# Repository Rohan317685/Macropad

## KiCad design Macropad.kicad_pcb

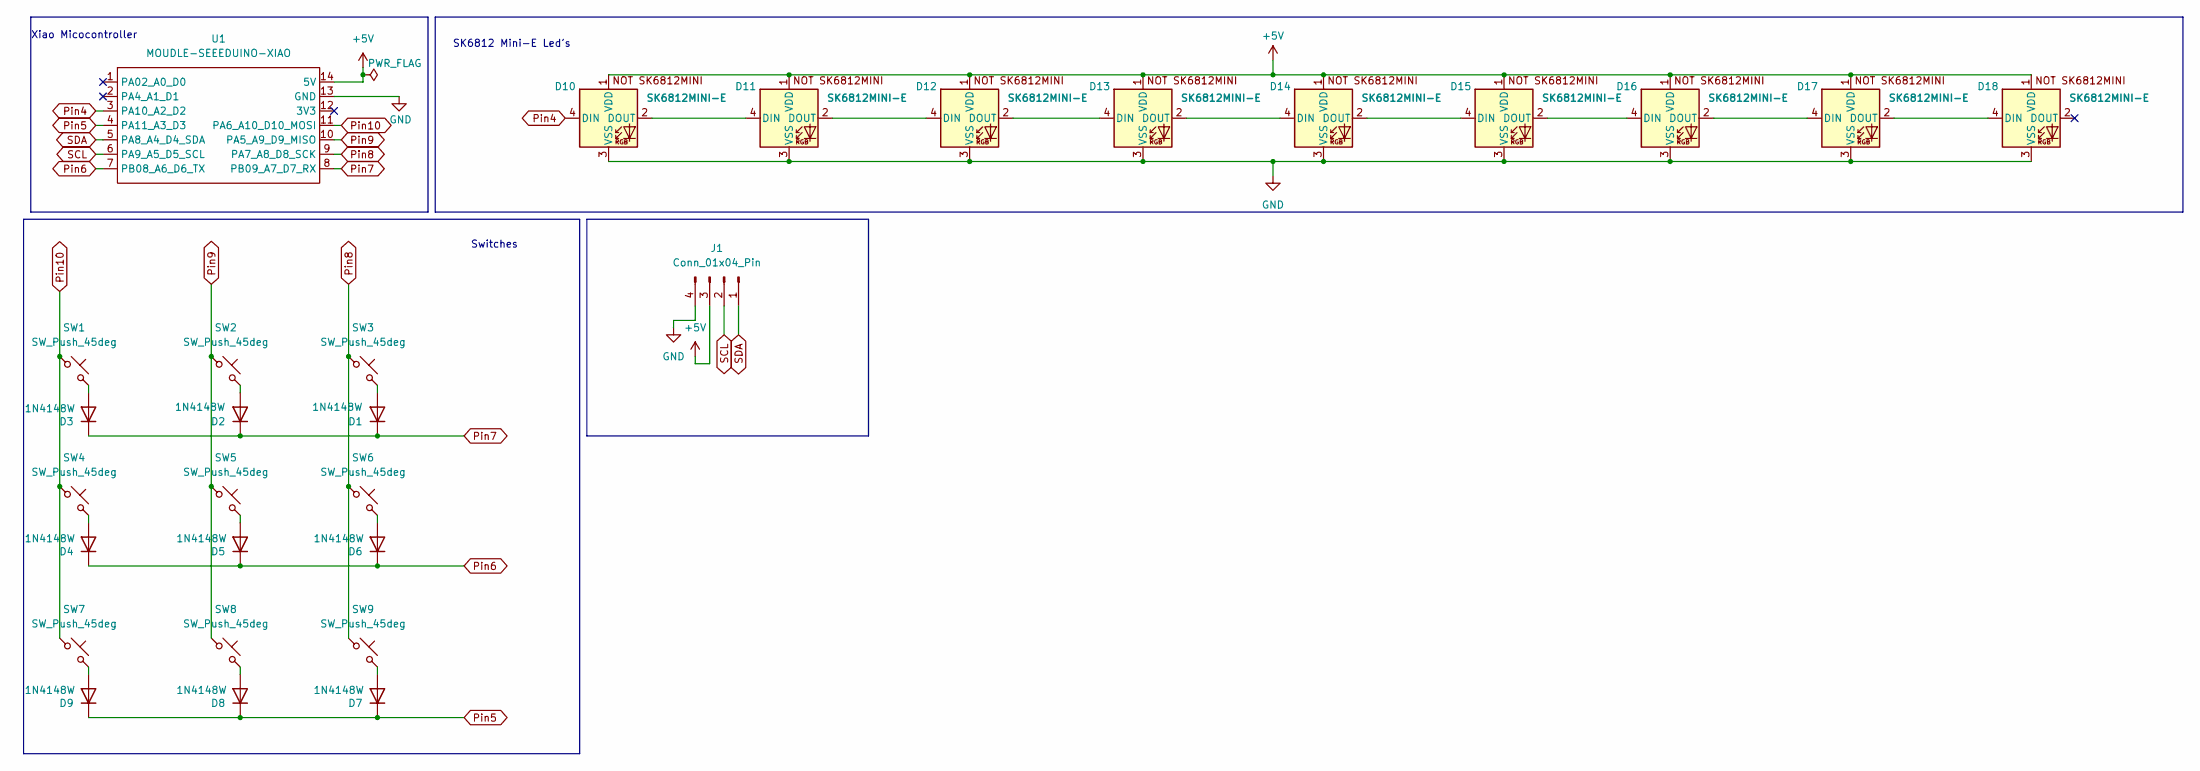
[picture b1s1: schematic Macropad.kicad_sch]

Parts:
D1, D2, D3, D4, D5, D6, D7, D8, D9: 1N4148W; D_SOD-123
D10, D11, D12, D13, D14, D15, D16, D17, D18: SK6812MINI-E; SK6812MINI-E_fixed
J1: Conn_01x04_Pin; SSD1306-0.91-OLED-4pin-128x32
SW1, SW2, SW3, SW4, SW5, SW6, SW7, SW8, SW9: SW_Push_45deg; SW_Cherry_MX_1.00u_PCB
U1: MOUDLE-SEEEDUINO-XIAO; XIAO-Generic-Hybrid-14P-2.54-21X17.8MM

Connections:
+5V: D10.1 (VDD), D11.1 (VDD), D12.1 (VDD), D13.1 (VDD), D14.1 (VDD), D15.1 (VDD), D16.1 (VDD), D17.1 (VDD), D18.1 (VDD), J1.3 (VCC), U1.14 (5V)
GND: D10.3 (VSS), D11.3 (VSS), D12.3 (VSS), D13.3 (VSS), D14.3 (VSS), D15.3 (VSS), D16.3 (VSS), D17.3 (VSS), D18.3 (VSS), J1.4 (GND), U1.13 (GND)
unnamed: D1.2 (A), SW3.2
unnamed: D2.2 (A), SW2.2
unnamed: D3.2 (A), SW1.2
unnamed: D4.2 (A), SW4.2
unnamed: D5.2 (A), SW5.2
unnamed: D6.2 (A), SW6.2
unnamed: D7.2 (A), SW9.2
unnamed: D8.2 (A), SW8.2
unnamed: D9.2 (A), SW7.2
unnamed: D10.2 (DOUT), D11.4 (DIN)
unnamed: D11.2 (DOUT), D12.4 (DIN)
unnamed: D12.2 (DOUT), D13.4 (DIN)
unnamed: D13.2 (DOUT), D14.4 (DIN)
unnamed: D14.2 (DOUT), D15.4 (DIN)
unnamed: D15.2 (DOUT), D16.4 (DIN)
unnamed: D16.2 (DOUT), D17.4 (DIN)
unnamed: D17.2 (DOUT), D18.4 (DIN)
Pin4: D10.4 (DIN), U1.3 (PA10_A2_D2)
Pin5: D7.1 (K), D8.1 (K), D9.1 (K), U1.4 (PA11_A3_D3)
Pin6: D4.1 (K), D5.1 (K), D6.1 (K), U1.7 (PB08_A6_D6_TX)
Pin7: D1.1 (K), D2.1 (K), D3.1 (K), U1.8 (PB09_A7_D7_RX)
Pin8: SW3.1, SW6.1, SW9.1, U1.9 (PA7_A8_D8_SCK)
Pin9: SW2.1, SW5.1, SW8.1, U1.10 (PA5_A9_D9_MISO)
Pin10: SW1.1, SW4.1, SW7.1, U1.11 (PA6_A10_D10_MOSI)
SCL: J1.2 (SCL), U1.6 (PA9_A5_D5_SCL)
SDA: J1.1 (SDA), U1.5 (PA8_A4_D4_SDA)

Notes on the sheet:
Switches
SK6812 Mini-E Led's
Xiao Micocontroller

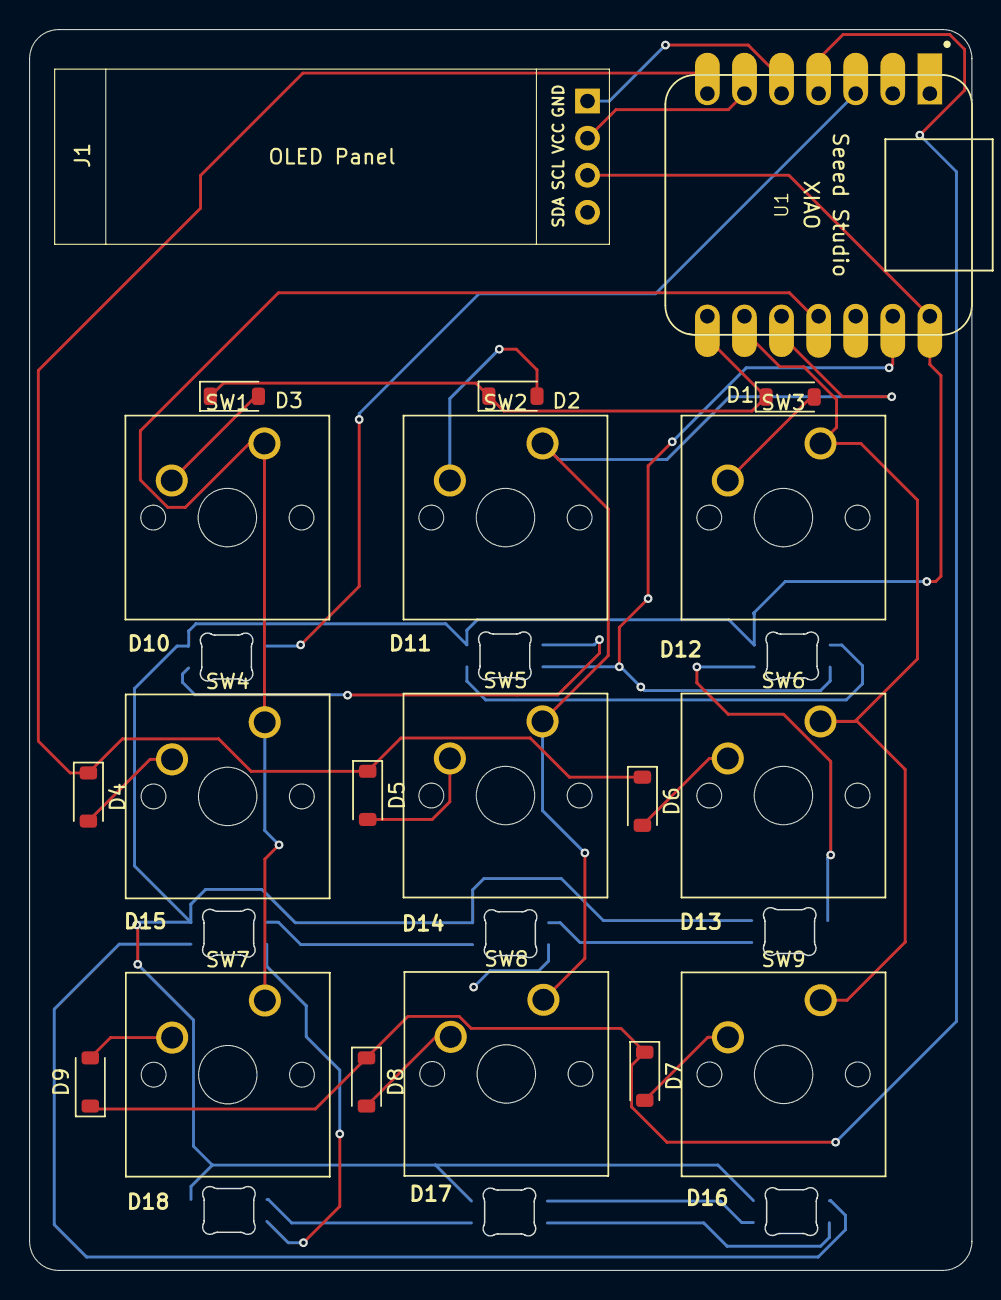
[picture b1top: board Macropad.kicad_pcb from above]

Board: 2 copper layers, 64.5 x 85.0 mm, 29 parts (0 on the bottom side), 28 nets.

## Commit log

2026-06-07 I RECOVERED MY PCB FILES RAHHHH
    IM NEVER GOING TO FORGET NOT TO COMMIT REGULARLY AGAIN
